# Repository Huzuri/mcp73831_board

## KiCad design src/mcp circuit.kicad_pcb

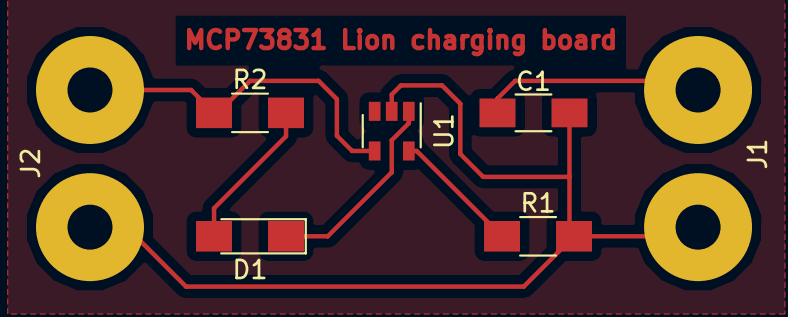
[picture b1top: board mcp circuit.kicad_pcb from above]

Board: 2 copper layers, 7 parts (0 on the bottom side), 6 nets.

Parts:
C1: 4.7uf; C_1206_HandSoldering
D1: led; LED_1206_HandSoldering
J1: battery in; SolderWirePad_2x_2-5mmDrill
J2: charge_in; SolderWirePad_2x_2-5mmDrill
R1: 2k; R_1206_HandSoldering
R2: 470; R_1206_HandSoldering
U1: MCP73831; SOT-23-5

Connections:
+5V: J2.2, R2.1, U1.4
GND: C1.2, J1.2, J2.1, R1.2, U1.2
unnamed: C1.1, J1.1, U1.3
unnamed: D1.1, U1.1
unnamed: D1.2, R2.2
unnamed: R1.1, U1.5

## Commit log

2018-10-29 added the kiacd files
